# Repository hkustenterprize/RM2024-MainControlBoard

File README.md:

<div align='center'>
    <h1>灵活, 小巧, 可靠</h1>
</div>

<div align='center'>
    <h2>RM2024香港科技大学ENTERPRIZE</h2>
</div>

<div align='center'>
    <h1>G4主控板硬件开源</h1>
</div>

<div align='center'>

</div>

> 设计者：xzm/贤梓铭 zxianaa@connect.ust.hk
>
> 指导/提议：jyc/EthenJ, jason chan, ry/EEASEE, ofr, gzl/Fallengold, zzy
>
> 香港科技大学ENTERPRIZE战队 robomasterhkust@gmail.com

## 开源内容

~~~
RM2024_MainControlBoard
├── image
├── PDF Schematic               > PDF格式的原理图
├── RM2024_G473_MCB             > 核心板工程文件
├── RM2024_G473_MCB_Debugger    > 调试小板工程文件
├── RM2024_G473_MCB_EngExtend   > 单板方案工程扩展板工程文件 by ofr
├── RM2024_G473_MCB_StdExtend   > 常规扩展板工程文件
├── RM2024_G473_MCB_Shim.step   > 一体3D打印垫片step文件 by tsl
├── RM2024-Template-G473.ioc    > CubeMX模板
├── LICENSE
└── README.md
~~~

开源工程文件设计软件为 KiCAD, 建议使用 **KiCAD 8.0** 打开, 可以导入 **立创EDA**

每个工程文件文件夹中的内容:

~~~
xxx
├── bom             > 焊接小工具, 由 "Interactive HTML BOM" 插件生成
├── production      > 生产文件, 由 "Fabrication Toolkit" 插件生成
├── xxx.kicad_pcb   > PCB
├── xxx.kicad_pro   > 主工程, 通过双击这个启动KiCAD
└── xxx.kicad_sch   > 原理图
~~~

## 方案简介

整套主控板分为核心板(下板)和扩展板(上板), 两板之间使用80pin BTB接口连接; 核心板包含所有核心芯片, 而扩展板一般只用于引出接口 (以及buzzer, laser等功能), 需要特殊功能时则用作功能扩展

- MCU: STM32G473VET6
- IMU: ICM-42688P
- 磁力计: LIS3MDLTR
- TTL (硬件流控): CH343P *2 
- FDCAN *3
- RS485 (硬件流控) *1
- FLASH: W25N01GVZEIG

## 项目背景 & 应用情况

在 RoboMaster 2024 赛季, 由于队内自研的上一代主控板 (F407) 已经无法满足对机器人控制的需求, 于是产生了设计新型主控板的需求

在经过反复考虑和对比后, 我们选择了STM32G473VET6作为主控芯片, 主要原因如下

- 共有三路FDCAN外设, 可以控制更多电机
- 支持RS485硬件流控功能, 提升板间通讯的稳定性
- 相较于H7系列复杂度较低, 开发难度与F4系列近似

同时, 新一代主控板也有缩小体积的需求, 整个主控板大小控制在 **60×40×21mm**, 与大疆C板相近, 便于机械安装

<div align='center'>

</div>

最终, G4主控板被应用于ENTERPRIZE战队本赛季所有新研发的机器人, 并且为 **工程机器人的单板方案** (左图) 和 **双头哨兵** (右图) 打下基础; 同时也实现了较强的稳定性, 在几场比赛中从未出现因硬件不稳定而导致的问题

## 硬件连接框图(简化)

## 技术细节

### UART

虽然STM32G473的FDCAN等外设数量较多, 但UART的数量却只有5个, 如果用传统的方法对UART和相应功能进行一一绑定, 那么UART数量则不足以实现所有需要的功能

为了解决此问题, G4主控板在设计时利用了MCU外设内部的 **MUX**, 比如 UART1 可以配置为 PC4/PC5 或 PE0/PE1, 再与相应功能进行绑定, 以此来实现在不同应用场景中适应不同需求的能力

同时, 对于同一功能, G4主控板也提供了可以从多个外设的访问的选项; 比如对于接收机, 可以通过软件配置来使用 UART1 或 UART3 来接受数据

下面是具体的UART引脚配置, 以A/B/C后缀来表示同一UART的不同配置方式:

|        | TX   | RX   | DE   | CTS  | RTS  | 功能          |
| -----  | ---- | ---- | ---- | ---- | ---- | ----          |
| UART1A | PC4  | PC5  | -    | -    | -    | 裁判系统/图传  |
| UART1B | PE0  | PE1  | -    | -    | -    | 通用          |
| UART1C | -    | PA10 | -    | -    | -    | 接收机        |
| UART2A | PA2  | PA3  | -    | PA0  | PA1  | TTL1          |
| UART2B | PD5  | PD6  | -    | -    | -    | 通用          |  
| UART3A | PD8  | PD9  | -    | PD11 | PD12 | TTL2          |
| UART3B | PB10 | PE15 | -    | -    | -    | 通用          |  
| UART3C | -    | PB11 | -    | -    | -    | 接收机        | 
| UART4  | PC10 | PC11 | PA15 | -    | -    | RS485        |   
| UART5  | PC12 | PD2  | -    | -    | -    | 裁判系统/图传 |

下面是部分机器人上的UART功能分配:

|                   | UART1 | UART2 | UART3 | UART4 | UART5 |
| -----             | ----  | ----  | ----  | ----  | ----  |
| 步兵云台 | [C] 接收机 | [A] TTL1 | RESV | RS485 | [A] 图传 |
| 英雄云台 | [C] 接收机 | [A] TTL1 | RESV | RS485 | [A] 图传 |
| 哨兵云台 | [C] 接收机 | [A] TTL1 | [A] TTL2 | RS485 | [A] 图传 |
| 工程(单板) | [A] 裁判系统 | [B] 总线舵机  |  [C] 接收机 | RS485 | [A] 图传|
| 通用底盘  | RESV | RESV | RESV | RS485 | 裁判系统 |

### IMU

经过对比测试, IMU选择ICM-42688P, 并配合加热电阻实现恒温

经过测试, 选用1206封装, 36ohm的电阻可以满足恒温50°C的需求; 经测试, **恒温后纯IMU姿态解算5分钟内漂移小于1°**

同时, SPI信号线串接82ohm电阻, **通信速率可以稳定20M**

### RS485

|       | TX/D | RX/R | DE   |
| ----- | ---- | ---- | ---- |
| RS485 | PC10 | PC11 | PA15 |

主控板集成RS485来提供板间通信功能, 相较于串口, RS485可以使通信更加稳定(特别是过滑环时)

RS485 Transceiver选用SN75176AD, 可替换为其他芯片; 用SM712进行保护

使用STM32G473的RS485硬件流控功能后, **板间通信速率最高可以达到4.8M, 丢包率小于0.09%**

### CAN (×3)

|       | TX   | RX   |
| ----- | ---- | ---- |
| CAN1  | PD1  | PD0  |
| CAN2  | PB6  | PB5  |
| CAN3  | PB4  | PB3  |

CAN Transceiver选用SIT1042T/3, 可替换为其他芯片; 使用ESD1CAN进行保护

### USB-TTL (×2)

|       | TX   | RX   | CTS  | RTS  |
| ----- | ---- | ---- | ---- | ---- |
| TTL1 (UART2A)  | PA2  | PA3  | PA0  | PA1  |
| TTL2 (UART3A)  | PD8  | PD9  | PD11 | PD12 |

USB-TTL选用CH343P, 连接了RTS/CTS引脚来实现硬件流控, 使用TPD4E1U06DCKR进行保护

经测试**全双工条件下单向速率稳定2M, 实测丢包率0.006%左右**

连接了ACT指示灯, 方便观察连接状态, 此功能上场时非常有用(观察MiniPC是否断连)

### FLASH

|       | NCS   | CLK   | IO0  | IO1  | IO2  | IO3  |
| ----- | ---- | ---- | ---- | ---- | ---- | ---- |
| MCU   | PD3  | PF10  | PD4  | PC2  | PD3  | PC7  |

主控板集成FLASH用于记录数据, 便于调试分析; 型号选用W25N01GVZEIG; 通过QSPI与MCU进行通信

### 接收机

G4主控板采用MCU内部反相, 无需外部反相电路, 使用TPD4E1U06DCKR进行保护

可以通过 PB11(UART3) 或 PA10(UART1) 接收信号, 防止其中一个串口被占用的情况

### 硬件ID检测

通过短接扩展板上的三个ID焊盘, 可以配置主控板的 ID 和 Master/Slave角色

通过在代码中加入ID验证步骤, 可以防止因烧错代码导致 RS485 Transceiver 烧毁等问题

## 供电系统

### 电源框图

### 设计细节及原因

#### 3V3_MCU

由Buck电路而非LDO降压产生, 原因是STM32G473耗电量较大, 使用LDO会有潜在的过热问题; 

同时, 主控板上没有高精度ADC的需求, 故Buck电路的纹波对主控板正常工作影响不大

#### 3V3_IMU

专门用于IMU和磁力计的 VDD 供电网络, 防止其他噪声干扰IMU和磁力计; 

注意IMU和磁力计的 VDDIO 由 3V3_MCU 提供, 防止芯片内部通信部分对电源产生潜在干扰

#### 3V3_IO

主要用于于外部直接产生交互的外设的VIO;

与 3V3_MCU 隔离, 主要原因是为了防止外部收发信号时对核心供电的干扰, 比如 CAN 和 TTL 都直接使用 3V3_IO 作为生成信号电平的电源

#### 3V3_SWD

队内发生过因烧录器LDO损坏而导致 5V 烧毁MCU, 因此与 3V3_MCU 隔离, 通过二极管接入5V网络并同时防止倒灌;

此设计也产生了一个缺陷: 当主控板仅由烧录器供电是, 有时会因为压降太大而导致烧录不正常, 因此建议在有MiniPC USB供电或24V供电的情况下进行代码烧录和调试

#### 电压采样

主控板对 24V 和 5V 电源网络进行了电压采样;

前者是为了监测 24V 真实电源电压, 可以得到一些粗略电压信息;

后者是通过检测微小电压差异来确定目前的供电方式 (利用Buck输出 5.2V, USB供电 5.0V, SWD供电三种情况导致的差异), 并且在状态不正常时报警 (比如可以检测24V转5V的Buck损坏)

### 纹波测试
5V

3V3_MCU

## 复刻注意事项

- 目前包含的SMT生产文件格式适用于嘉立创, 如有需要请重新生成
- BTB很脆弱, 避免在不垫垫片的情况下安装
- 焊接IMU后不要用超声波洗板
- 如有任何问题, 欢迎联系 zxianaa@connect.ust.hk; wx: xianziming0531

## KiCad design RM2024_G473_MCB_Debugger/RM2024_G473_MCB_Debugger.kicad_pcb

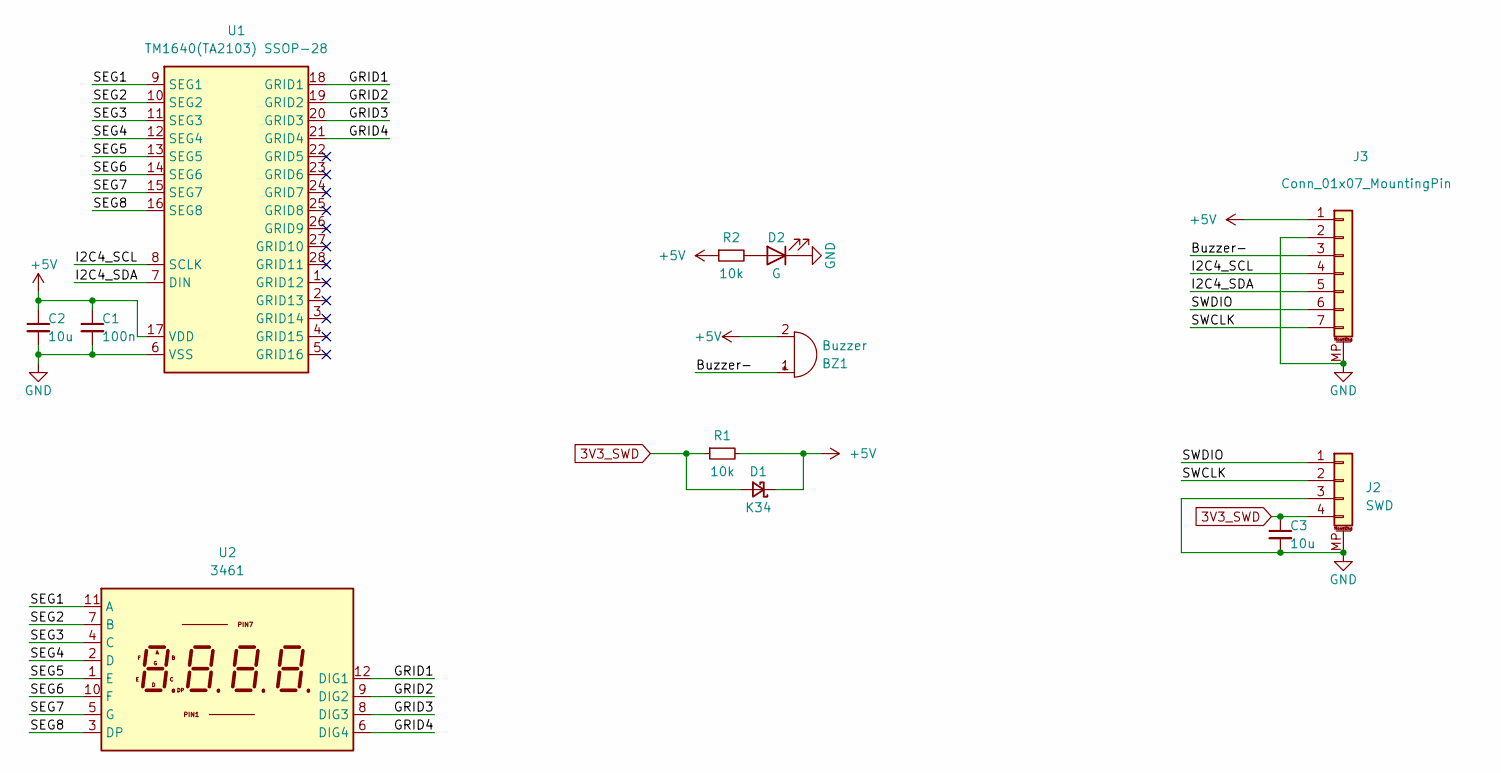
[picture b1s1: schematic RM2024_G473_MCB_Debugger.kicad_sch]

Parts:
BZ1: Buzzer; MLT-9032
C1: 100n; C_0603_1608Metric
C2, C3: 10u; C_0603_1608Metric
D1: K34; D_SMF
D2: G; LED_0603_1608Metric
J2: SWD; Molex_PicoBlade_53398-0471_1x04-1MP_P1.25mm_Vertical
J3: Conn_01x07_MountingPin; JST_GH_SM07B-GHS-TB_1x07-1MP_P1.25mm_Horizontal
R1, R2: 10k; R_0603_1608Metric
U1: TM1640(TA2103) SSOP-28; SSOP-28_3.9x9.9mm_P0.635mm
U2: 3461; LED-8888-3461

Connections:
3V3_SWD: C3.1, D1.2 (A), J2.4, R1.1
+5V: BZ1.2 (+), C1.1, C2.1, D1.1 (K), J3.1, R1.2, R2.1, U1.17 (VDD)
/Buzzer-: BZ1.1 (-), J3.3
/GRID1: U1.18 (GRID1), U2.12 (DIG1)
/GRID2: U1.19 (GRID2), U2.9 (DIG2)
/GRID3: U1.20 (GRID3), U2.8 (DIG3)
/GRID4: U1.21 (GRID4), U2.6 (DIG4)
/I2C4_SCL: J3.4, U1.8 (SCLK)
/I2C4_SDA: J3.5, U1.7 (DIN)
/SEG1: U1.9 (SEG1), U2.11 (A)
/SEG2: U1.10 (SEG2), U2.7 (B)
/SEG3: U1.11 (SEG3), U2.4 (C)
/SEG4: U1.12 (SEG4), U2.2 (D)
/SEG5: U1.13 (SEG5), U2.1 (E)
/SEG6: U1.14 (SEG6), U2.10 (F)
/SEG7: U1.15 (SEG7), U2.5 (G)
/SEG8: U1.16 (SEG8), U2.3 (DP)
/SWCLK: J2.2, J3.7
/SWDIO: J2.1, J3.6
GND: C1.2, C2.2, C3.2, D2.1 (K), J2.3, J2.MP (MountPin), J3.2, J3.MP (MountPin), U1.6 (VSS)
unnamed: D2.2 (A), R2.2

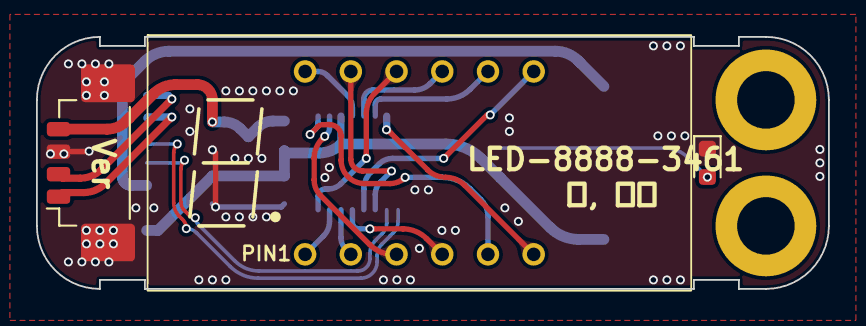
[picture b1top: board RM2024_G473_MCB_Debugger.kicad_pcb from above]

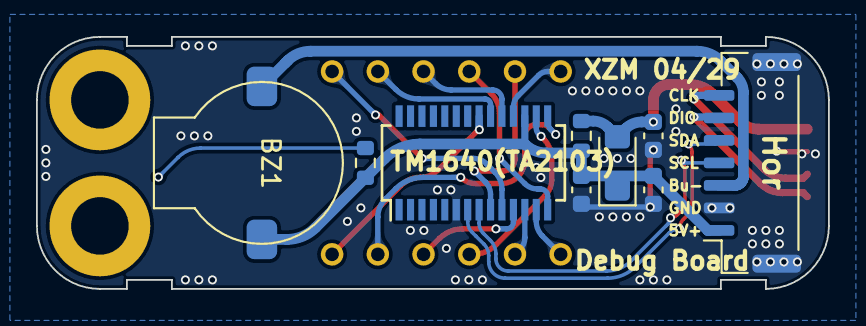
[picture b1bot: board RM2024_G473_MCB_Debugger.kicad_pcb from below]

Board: 2 copper layers, 44.0 x 14.0 mm, 12 parts (9 on the bottom side), 21 nets.

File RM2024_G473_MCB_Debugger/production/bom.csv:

Designator,Footprint,Quantity,Value,LCSC Part #
BZ1,MLT-9032,1,Buzzer,
C1,0603,1,100n,
"C2, C3",0603,2,10u,
D1,D_SMF,1,K34,
D2,0603,1,G,
J2,Molex_PicoBlade_53398-0471_1x04-1MP_P1.25mm_Vertical,1,SWD,
J3,JST_GH_SM07B-GHS-TB_1x07-1MP_P1.25mm_Horizontal,1,Conn_01x07_MountingPin,
"R1, R2",0603,2,10k,
U1,SSOP-28_3.9x9.9mm_P0.635mm,1,TM1640(TA2103) SSOP-28,
U2,LED-8888-3461,1,3461,

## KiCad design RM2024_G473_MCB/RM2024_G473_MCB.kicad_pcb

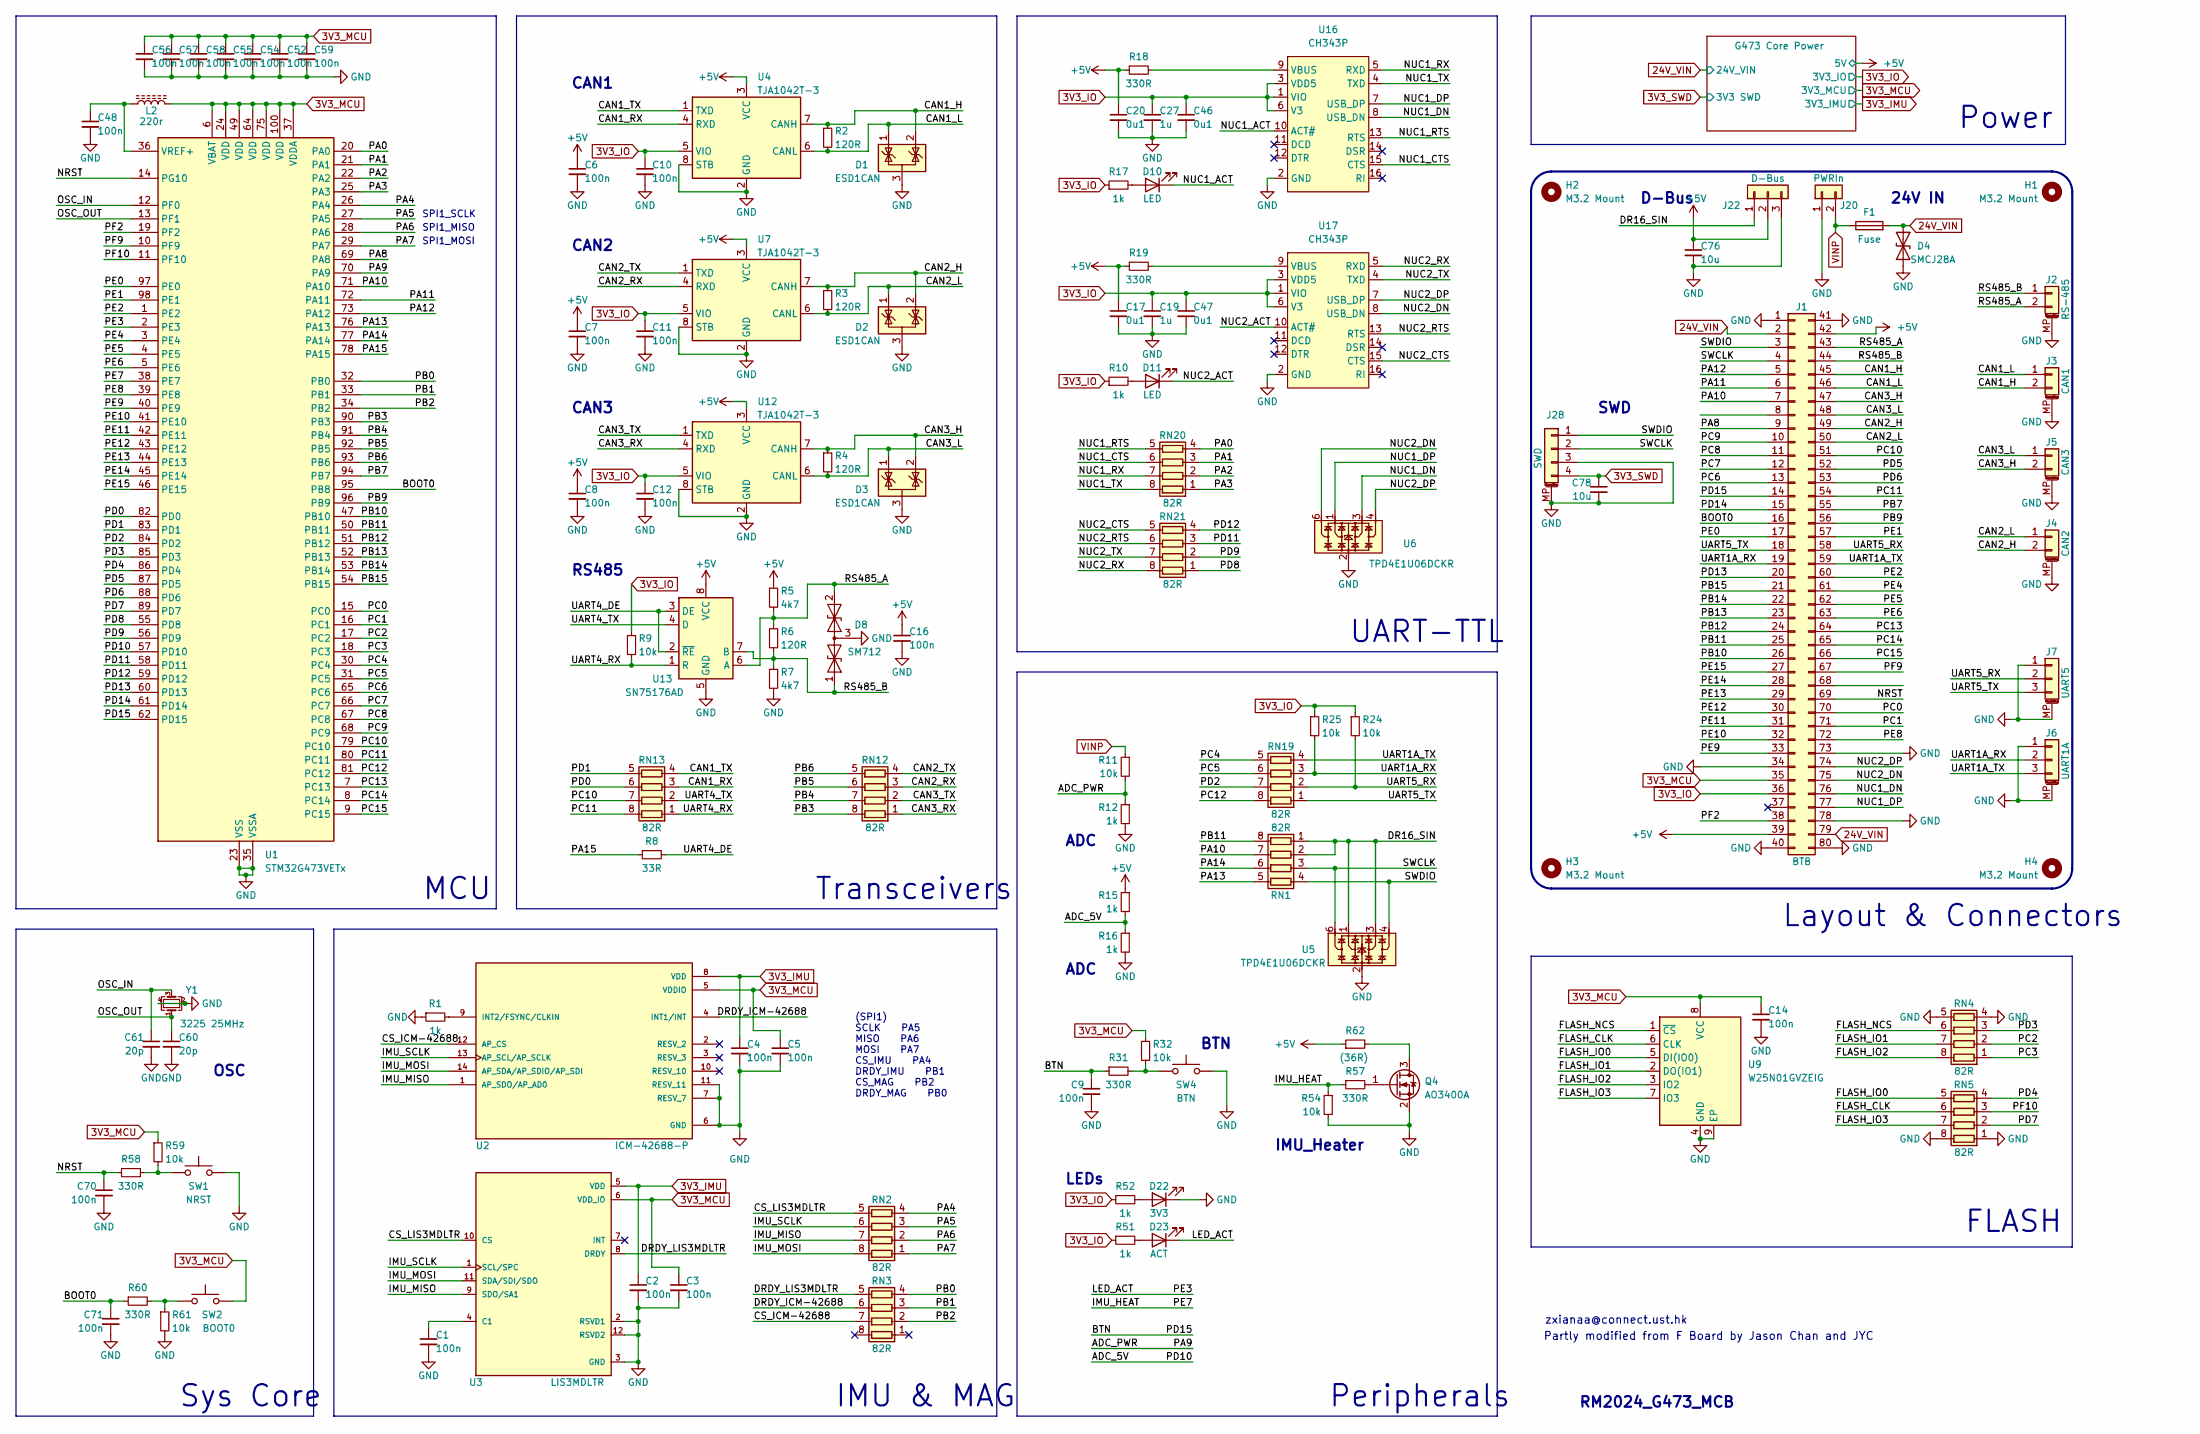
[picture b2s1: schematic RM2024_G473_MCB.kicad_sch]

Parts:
C1, C2, C3, C4, C5, C6, C7, C8, C9, C10, C11, C12, C14, C16, C48, C52, C54, C55, C56, C57, C58, C59, C70, C71: 100n; C_0603_1608Metric
C17, C20, C46, C47: 0u1; C_0603_1608Metric
C19, C27: 1u; C_0603_1608Metric
C60, C61: 20p; C_0603_1608Metric
C76, C78: 10u; C_0603_1608Metric
D1, D2, D3: ESD1CAN; SOT-23
D4: SMCJ28A; D_SMC
D8: SM712; SOT-23
D10, D11: LED; LED_0603_1608Metric
D22: 3V3; LED_0603_1608Metric
D23: ACT; LED_0603_1608Metric
F1: Fuse; Fuse_1206_3216Metric
H1, H2, H3, H4: M3.2 Mount; MountingHole_3.2mm_M3_DIN965_Pad
J1: BTB; BTB_P0.8mm_2x40pin_F
J2: RS-485; JST_GH_SM02B-GHS-TB_1x02-1MP_P1.25mm_Horizontal
J3: CAN1; JST_GH_SM02B-GHS-TB_1x02-1MP_P1.25mm_Horizontal
J4: CAN2; JST_GH_SM02B-GHS-TB_1x02-1MP_P1.25mm_Horizontal
J5: CAN3; JST_GH_SM02B-GHS-TB_1x02-1MP_P1.25mm_Horizontal
J6: UART1A; JST_GH_SM03B-GHS-TB_1x03-1MP_P1.25mm_Horizontal
J7: UART5; JST_GH_SM03B-GHS-TB_1x03-1MP_P1.25mm_Horizontal
J20: PWRIn; AMASS_XT30U-M_1x02_P5.0mm_Vertical
J22: D-Bus; PinHeader_1x03_P2.54mm_Vertical
J28: SWD; Molex_PicoBlade_53261-0471_1x04-1MP_P1.25mm_Horizontal
L2: 220r; L_0603_1608Metric
Q4: AO3400A; SOT-23
R1, R10, R12, R15, R16, R17, R51, R52: 1k; R_0603_1608Metric
R2, R3, R4, R6: 120R; R_0603_1608Metric
R5, R7: 4k7; R_0603_1608Metric
R8: 33R; R_0603_1608Metric
R9, R11, R24, R25, R32, R54, R59, R61: 10k; R_0603_1608Metric
R18, R19, R31, R57, R58, R60: 330R; R_0603_1608Metric
R62: (36R); R_1206_3216Metric
RN1, RN2, RN3, RN4, RN5, RN12, RN13, RN19, RN20, RN21: 82R; R_Array_Concave_4x0603
SW1: NRST; Panasonic_EVQPUL_EVQPUC
SW2: BOOT0; Panasonic_EVQPUL_EVQPUC
SW4: BTN; Panasonic_EVQPUL_EVQPUC
U1: STM32G473VETx; LQFP-100_14x14mm_P0.5mm
U2: ICM-42688-P; PQFN50P300X250X97-14N; PARTREV 1.2
U3: LIS3MDLTR; XDCR_LIS3MDLTR; PARTREV 6
U4, U7, U12: TJA1042T-3; SOIC-8_3.9x4.9mm_P1.27mm
U5, U6: TPD4E1U06DCKR; SOT-363_SC-70-6
U9: W25N01GVZEIG; WSON-8-1EP_8x6mm_P1.27mm_EP3.4x4.3mm
U13: SN75176AD; SOIC-8_3.9x4.9mm_P1.27mm
U16, U17: CH343P; TQFN-16-1EP_3x3mm_P0.5mm_EP1.6x1.6mm
Y1: 3225 25MHz; Crystal_SMD_3225-4Pin_3.2x2.5mm

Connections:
3V3_IMU: C2.1, C4.1, U2.8 (VDD), U3.5 (VDD); also elsewhere on the board
3V3_IO: C10.1, C11.1, C12.1, C19.1, C27.1, C46.1, C47.1, J1.36, R9.1, R10.1, R17.1, R24.1, R25.1, R51.1, R52.1, U4.5 (VIO), U7.5 (VIO), U12.5 (VIO), U16.1 (VIO), U16.3 (VDD5), U16.6 (V3), U17.1 (VIO), U17.3 (VDD5), U17.6 (V3); also elsewhere on the board
3V3_MCU: C3.1, C5.1, C14.1, C52.1, C54.1, C55.1, C56.1, C57.1, C58.1, C59.1, J1.35, L2.2, R32.1, R59.1, SW2.2, U1.6 (VBAT), U1.24 (VDD), U1.37 (VDDA), U1.49 (VDD), U1.64 (VDD), U1.75 (VDD), U1.100 (VDD), U2.5 (VDDIO), U3.6 (VDD_IO), U9.8 (VCC); also elsewhere on the board
3V3_SWD: C78.1, J28.4; also elsewhere on the board
24V_VIN: D4.1 (A1), F1.2, J1.2, J1.79; also elsewhere on the board
+5V: C6.1, C7.1, C8.1, C16.1, C17.1, C20.1, C76.1, J1.39, J1.42, J22.2, R5.1, R15.1, R18.1, R19.1, R62.1, U4.3 (VCC), U7.3 (VCC), U12.3 (VCC), U13.8 (VCC); also elsewhere on the board
/ADC_5V: R15.2, R16.1, U1.57 (PD10)
/ADC_PWR: R11.2, R12.1, U1.70 (PA9)
/BOOT0: C71.1, J1.16, R60.1, U1.95 (PB8)
/BTN: C9.1, J1.14, R31.1, U1.62 (PD15)
/CAN1_H: D1.2 (K), J1.45, J3.2, R2.1, U4.7 (CANH)
/CAN1_L: D1.1 (K), J1.46, J3.1, R2.2, U4.6 (CANL)
/CAN1_RX: RN13.3 (R3.1), U4.4 (RXD)
/CAN1_TX: RN13.4 (R4.1), U4.1 (TXD)
/CAN2_H: D2.2 (K), J1.49, J4.2, R3.1, U7.7 (CANH)
/CAN2_L: D2.1 (K), J1.50, J4.1, R3.2, U7.6 (CANL)
/CAN2_RX: RN12.3 (R3.1), U7.4 (RXD)
/CAN2_TX: RN12.4 (R4.1), U7.1 (TXD)
/CAN3_H: D3.2 (K), J1.47, J5.2, R4.1, U12.7 (CANH)
/CAN3_L: D3.1 (K), J1.48, J5.1, R4.2, U12.6 (CANL)
/CAN3_RX: RN12.1 (R1.1), U12.4 (RXD)
/CAN3_TX: RN12.2 (R2.1), U12.1 (TXD)
/CS_ICM-42688: RN3.7 (R2.2), U2.12 (AP_CS)
/CS_LIS3MDLTR: RN2.5 (R4.2), U3.10 (CS)
/DR16_SIN: J22.1, RN1.1 (R1.1), RN1.2 (R2.1), U5.1, U5.3
/DRDY_ICM-42688: RN3.6 (R3.2), U2.4 (INT1/INT)
/DRDY_LIS3MDLTR: RN3.5 (R4.2), U3.8 (DRDY)
/FLASH_CLK: RN5.6 (R3.2), U9.6 (CLK)
/FLASH_IO0: RN5.5 (R4.2), U9.5 (DI(IO0))
/FLASH_IO1: RN4.7 (R2.2), U9.2 (DO(IO1))
/FLASH_IO2: RN4.8 (R1.2), U9.3 (IO2)
/FLASH_IO3: RN5.7 (R2.2), U9.7 (IO3)
/FLASH_NCS: RN4.6 (R3.2), U9.1 (~CS)
/IMU_HEAT: R54.1, R57.1, U1.38 (PE7)
/IMU_MISO: RN2.7 (R2.2), U2.1 (AP_SDO/AP_AD0), U3.9 (SDO/SA1)
/IMU_MOSI: RN2.8 (R1.2), U2.14 (AP_SDA/AP_SDIO/AP_SDI), U3.11 (SDA/SDI/SDO)
/IMU_SCLK: RN2.6 (R3.2), U2.13 (AP_SCL/AP_SCLK), U3.1 (SCL/SPC)
/LED_ACT: D23.1 (K), U1.2 (PE3)
/NRST: C70.1, J1.69, R58.1, U1.14 (PG10)
/NUC1_ACT: D10.1 (K), U16.10 (ACT#)
/NUC1_CTS: RN20.6 (R3.2), U16.15 (CTS)
/NUC1_DN: J1.76, U6.3, U16.8 (USB_DN)
/NUC1_DP: J1.77, U6.1, U16.7 (USB_DP)
/NUC1_RTS: RN20.5 (R4.2), U16.13 (RTS)
/NUC1_RX: RN20.7 (R2.2), U16.5 (RXD)
/NUC1_TX: RN20.8 (R1.2), U16.4 (TXD)
/NUC2_ACT: D11.1 (K), U17.10 (ACT#)
/NUC2_CTS: RN21.5 (R4.2), U17.15 (CTS)
/NUC2_DN: J1.75, U6.6, U17.8 (USB_DN)
/NUC2_DP: J1.74, U6.4, U17.7 (USB_DP)
/NUC2_RTS: RN21.6 (R3.2), U17.13 (RTS)
/NUC2_RX: RN21.8 (R1.2), U17.5 (RXD)
/NUC2_TX: RN21.7 (R2.2), U17.4 (TXD)
/OSC_IN: C61.1, U1.12 (PF0), Y1.3
/OSC_OUT: C60.1, U1.13 (PF1), Y1.1
/PA0: RN20.4 (R4.1), U1.20 (PA0)
/PA1: RN20.3 (R3.1), U1.21 (PA1)
/PA2: RN20.2 (R2.1), U1.22 (PA2)
/PA3: RN20.1 (R1.1), U1.25 (PA3)
/PA4: RN2.4 (R4.1), U1.26 (PA4)
/PA5: RN2.3 (R3.1), U1.27 (PA5)
/PA6: RN2.2 (R2.1), U1.28 (PA6)
/PA7: RN2.1 (R1.1), U1.29 (PA7)
/PA8: J1.9, U1.69 (PA8)
/PA10: J1.7, RN1.7 (R2.2), U1.71 (PA10)
/PA11: J1.6, U1.72 (PA11)
/PA12: J1.5, U1.73 (PA12)
/PA13: RN1.5 (R4.2), U1.76 (PA13)
/PA14: RN1.6 (R3.2), U1.77 (PA14)
/PA15: R8.1, U1.78 (PA15)
/PB0: RN3.4 (R4.1), U1.32 (PB0)
/PB1: RN3.3 (R3.1), U1.33 (PB1)
/PB2: RN3.2 (R2.1), U1.34 (PB2)
/PB3: RN12.8 (R1.2), U1.90 (PB3)
/PB4: RN12.7 (R2.2), U1.91 (PB4)
/PB5: RN12.6 (R3.2), U1.92 (PB5)
/PB6: RN12.5 (R4.2), U1.93 (PB6)
/PB7: J1.55, U1.94 (PB7)
/PB9: J1.56, U1.96 (PB9)
/PB10: J1.26, U1.47 (PB10)
/PB11: J1.25, RN1.8 (R1.2), U1.50 (PB11)
/PB12: J1.24, U1.51 (PB12)
/PB13: J1.23, U1.52 (PB13)
/PB14: J1.22, U1.53 (PB14)
/PB15: J1.21, U1.54 (PB15)
/PC0: J1.70, U1.15 (PC0)
/PC1: J1.71, U1.16 (PC1)
/PC2: RN4.2 (R2.1), U1.17 (PC2)
/PC3: RN4.1 (R1.1), U1.18 (PC3)
/PC4: RN19.5 (R4.2), U1.30 (PC4)
/PC5: RN19.6 (R3.2), U1.31 (PC5)
/PC6: J1.13, U1.65 (PC6)
/PC7: J1.12, U1.66 (PC7)
/PC8: J1.11, U1.67 (PC8)
/PC9: J1.10, U1.68 (PC9)
/PC10: J1.51, RN13.7 (R2.2), U1.79 (PC10)
/PC11: J1.54, RN13.8 (R1.2), U1.80 (PC11)
/PC12: RN19.8 (R1.2), U1.81 (PC12)
/PC13: J1.64, U1.7 (PC13)
/PC14: J1.65, U1.8 (PC14)
/PC15: J1.66, U1.9 (PC15)
/PD0: RN13.6 (R3.2), U1.82 (PD0)
/PD1: RN13.5 (R4.2), U1.83 (PD1)
/PD2: RN19.7 (R2.2), U1.84 (PD2)
/PD3: RN4.3 (R3.1), U1.85 (PD3)
/PD4: RN5.4 (R4.1), U1.86 (PD4)
/PD5: J1.52, U1.87 (PD5)
/PD6: J1.53, U1.88 (PD6)
/PD7: RN5.2 (R2.1), U1.89 (PD7)
/PD8: RN21.1 (R1.1), U1.55 (PD8)
/PD9: RN21.2 (R2.1), U1.56 (PD9)
/PD11: RN21.3 (R3.1), U1.58 (PD11)
/PD12: RN21.4 (R4.1), U1.59 (PD12)
/PD13: J1.20, U1.60 (PD13)
/PD14: J1.15, U1.61 (PD14)
/PE0: J1.17, U1.97 (PE0)
/PE1: J1.57, U1.98 (PE1)
/PE2: J1.60, U1.1 (PE2)
/PE4: J1.61, U1.3 (PE4)
/PE5: J1.62, U1.4 (PE5)
/PE6: J1.63, U1.5 (PE6)
/PE8: J1.72, U1.39 (PE8)
/PE9: J1.33, U1.40 (PE9)
/PE10: J1.32, U1.41 (PE10)
/PE11: J1.31, U1.42 (PE11)
/PE12: J1.30, U1.43 (PE12)
/PE13: J1.29, U1.44 (PE13)
/PE14: J1.28, U1.45 (PE14)
/PE15: J1.27, U1.46 (PE15)
/PF2: J1.38, U1.19 (PF2)
/PF9: J1.67, U1.10 (PF9)
/PF10: RN5.3 (R3.1), U1.11 (PF10)
/RS485_A: D8.2 (A2), J1.43, J2.2, R5.2, R6.1, U13.6 (A)
/RS485_B: D8.1 (A1), J1.44, J2.1, R6.2, R7.1, U13.7 (B)
/SWCLK: J1.4, J28.2, RN1.3 (R3.1), U5.6
/SWDIO: J1.3, J28.1, RN1.4 (R4.1), U5.4
/UART1A_RX: J1.19, J6.2, R25.2, RN19.3 (R3.1)
/UART1A_TX: J1.59, J6.3, RN19.4 (R4.1)
/UART4_DE: R8.2, U13.2 (~RE), U13.3 (DE)
/UART4_RX: R9.2, RN13.1 (R1.1), U13.1 (R)
/UART4_TX: RN13.2 (R2.1), U13.4 (D)
/UART5_RX: J1.58, J7.2, R24.2, RN19.2 (R2.1)
/UART5_TX: J1.18, J7.3, RN19.1 (R1.1)
GND: C1.2, C2.2, C3.2, C4.2, C5.2, C6.2, C7.2, C8.2, C9.2, C10.2, C11.2, C12.2, C14.2, C16.2, C17.2, C19.2, C20.2, C27.2, C46.2, C47.2, C48.2, C52.2, C54.2, C55.2, C56.2, C57.2, C58.2, C59.2, C60.2, C61.2, C70.2, C71.2, C76.2, C78.2, D1.3 (A), D2.3 (A), D3.3 (A), D4.2 (A2), D8.3 (common), D22.1 (K), J1.1, J1.34, J1.40, J1.41, J1.73, J1.78, J1.80, J2.MP (MountPin), J3.MP (MountPin), J4.MP (MountPin), J5.MP (MountPin), J6.1, J6.MP (MountPin), J7.1, J7.MP (MountPin), J20.1, J22.3, J28.3, J28.MP (MountPin), Q4.2 (S), R1.1, R7.2, R12.2, R16.2, R54.2, R61.2, RN4.4 (R4.1), RN4.5 (R4.2), RN5.1 (R1.1), RN5.8 (R1.2), SW1.2, SW4.2, U1.23 (VSS), U1.35 (VSSA), U1.48 (VSS), U1.63 (VSS), U1.74 (VSS), U1.99 (VSS), U2.6 (GND), U2.7 (RESV_7), U2.11 (RESV_11), U3.2 (RSVD1), U3.3 (GND), U3.12 (RSVD2), U4.2 (GND), U4.8 (STB), U5.2, U6.2, U7.2 (GND), U7.8 (STB), U9.4 (GND), U9.9 (EP), U12.2 (GND), U12.8 (STB), U13.5 (GND), U16.2 (GND), U16.17 (GND), U17.2 (GND), U17.17 (GND), Y1.2, Y1.4; also elsewhere on the board
unnamed: D10.2 (A), R17.2
unnamed: D11.2 (A), R10.2
unnamed: D22.2 (A), R52.2
unnamed: D23.2 (A), R51.2
unnamed: Q4.3 (D), R62.2
unnamed: Q4.1 (G), R57.2
unnamed: R31.2, R32.2, SW4.1
unnamed: R58.2, R59.2, SW1.1
unnamed: R60.2, R61.1, SW2.1
unnamed: C48.1, L2.1, U1.36 (VREF+)
unnamed: R1.2, U2.9 (INT2/FSYNC/CLKIN)
unnamed: C1.1, U3.4 (C1)
unnamed: R18.2, U16.9 (VBUS)
unnamed: R19.2, U17.9 (VBUS)
VINP: F1.1, J20.2, R11.1

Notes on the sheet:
SPI1_MOSI
ADC
(SPI1) SCLK PA5 MISO PA6 MOSI PA7 CS_IMU PA4 DRDY_IMU PB1 CS_MAG PB2 DRDY_MAG PB0
BTN
FLASH
OSC
IMU & MAG
Power
CAN1
24V IN
IMU_Heater
Layout & Connectors
Transceivers
Partly modified from F Board by Jason Chan and JYC
CAN3
RS485
SWD
SPI1_SCLK
Peripherals
RM2024_G473_MCB
MCU
Sys Core
SPI1_MISO
UART-TTL
LEDs
D-Bus
zxianaa@connect.ust.hk
CAN2

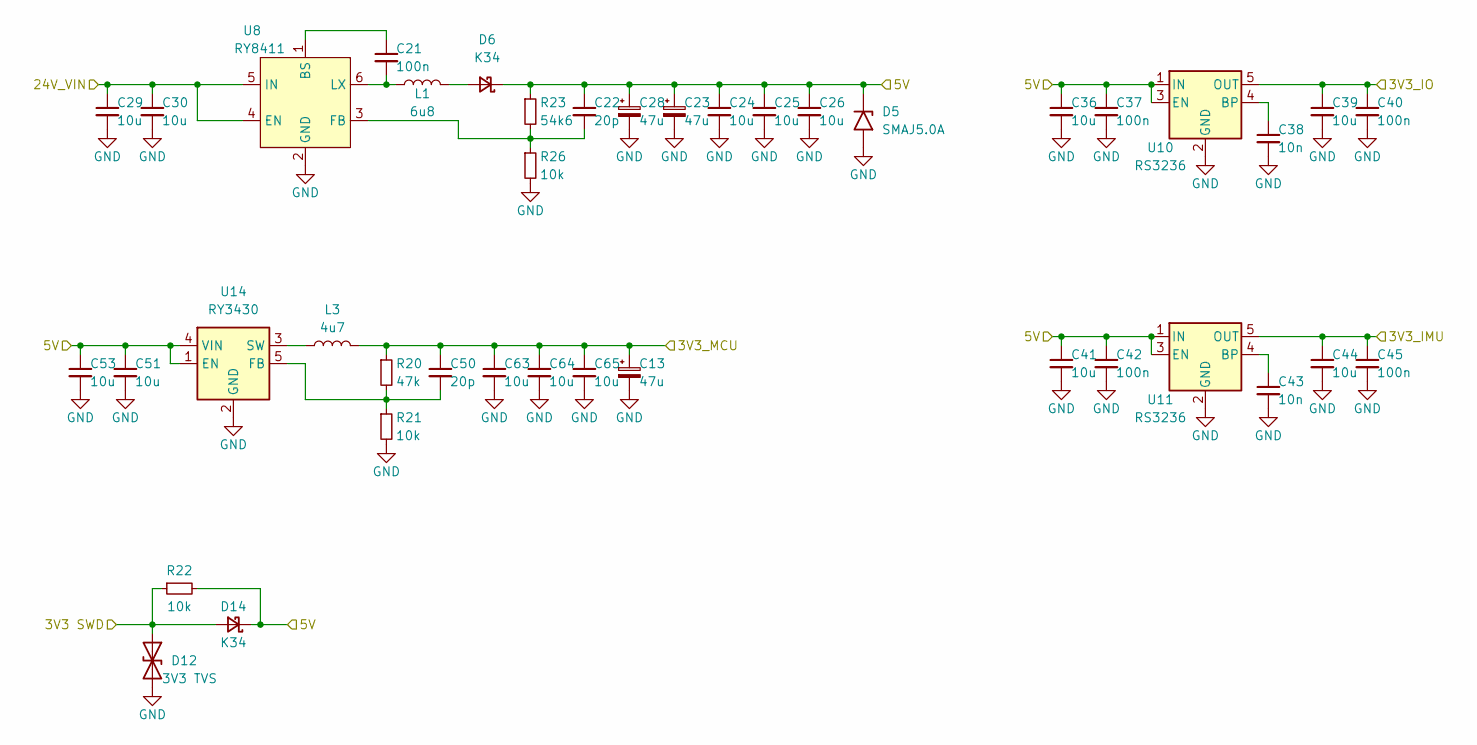
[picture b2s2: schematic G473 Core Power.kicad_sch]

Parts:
C13, C23, C28: 47u; CP_EIA-3216-18_Kemet-A_Pad1.58x1.35mm_HandSolder
C21, C37, C40, C42, C45: 100n; C_0603_1608Metric
C22, C50: 20p; C_0603_1608Metric
C24, C25, C26, C29, C30: 10u; C_1206_3216Metric
C36, C39, C41, C44, C51, C53, C63, C64, C65: 10u; C_0603_1608Metric
C38, C43: 10n; C_0603_1608Metric
D5: SMAJ5.0A; D_SMA
D6, D14: K34; D_SMF
D12: 3V3 TVS; D_SMF
L1: 6u8; L_Sunlord_MWSA0402S
L3: 4u7; L_Sunlord_MWSA0402S
R20: 47k; R_0603_1608Metric
R21, R22, R26: 10k; R_0603_1608Metric
R23: 54k6; R_0603_1608Metric
U8: RY8411; SOT-23-6
U10, U11: RS3236; SOT-23-5
U14: RY3430; SOT-23-5

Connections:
3V3_IMU: C44.1, C45.1, U11.5 (OUT); also elsewhere on the board
3V3_IO: C39.1, C40.1, U10.5 (OUT); also elsewhere on the board
3V3_MCU: C13.1, C50.1, C63.1, C64.1, C65.1, L3.2, R20.1; also elsewhere on the board
3V3_SWD: D12.1 (A1), D14.2 (A), R22.1; also elsewhere on the board
24V_VIN: C29.1, C30.1, U8.4 (EN), U8.5 (IN); also elsewhere on the board
+5V: C22.1, C23.1, C24.1, C25.1, C26.1, C28.1, C36.1, C37.1, C41.1, C42.1, C51.1, C53.1, D5.1 (A1), D6.1 (K), D14.1 (K), R22.2, R23.1, U10.1 (IN), U10.3 (EN), U11.1 (IN), U11.3 (EN), U14.1 (EN), U14.4 (VIN); also elsewhere on the board
GND: C13.2, C23.2, C24.2, C25.2, C26.2, C28.2, C29.2, C30.2, C36.2, C37.2, C38.2, C39.2, C40.2, C41.2, C42.2, C43.2, C44.2, C45.2, C51.2, C53.2, C63.2, C64.2, C65.2, D5.2 (A2), D12.2 (A2), R21.2, R26.2, U8.2 (GND), U10.2 (GND), U11.2 (GND), U14.2 (GND); also elsewhere on the board
unnamed: D6.2 (A), L1.2
unnamed: C21.1, U8.1 (BS)
unnamed: C22.2, R23.2, R26.1, U8.3 (FB)
unnamed: C21.2, L1.1, U8.6 (LX)
unnamed: C38.1, U10.4 (BP)
unnamed: C43.1, U11.4 (BP)
unnamed: C50.2, R20.2, R21.1, U14.5 (FB)
unnamed: L3.1, U14.3 (SW)

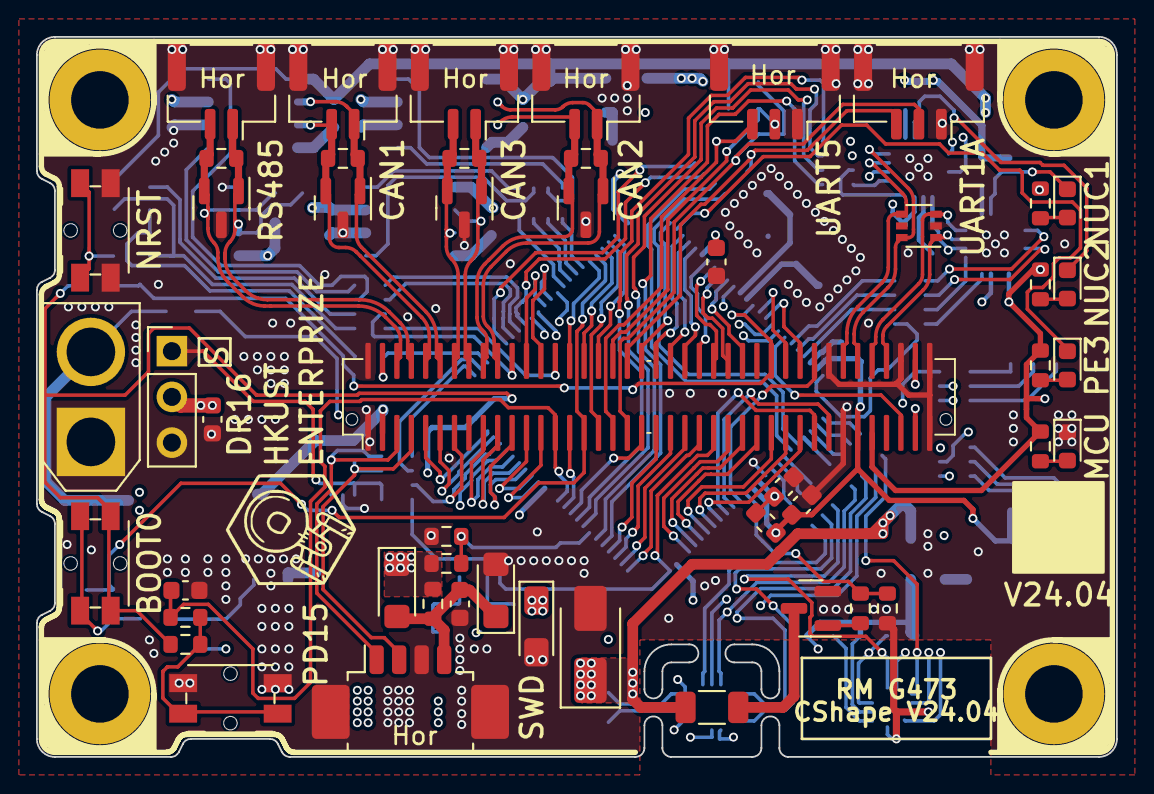
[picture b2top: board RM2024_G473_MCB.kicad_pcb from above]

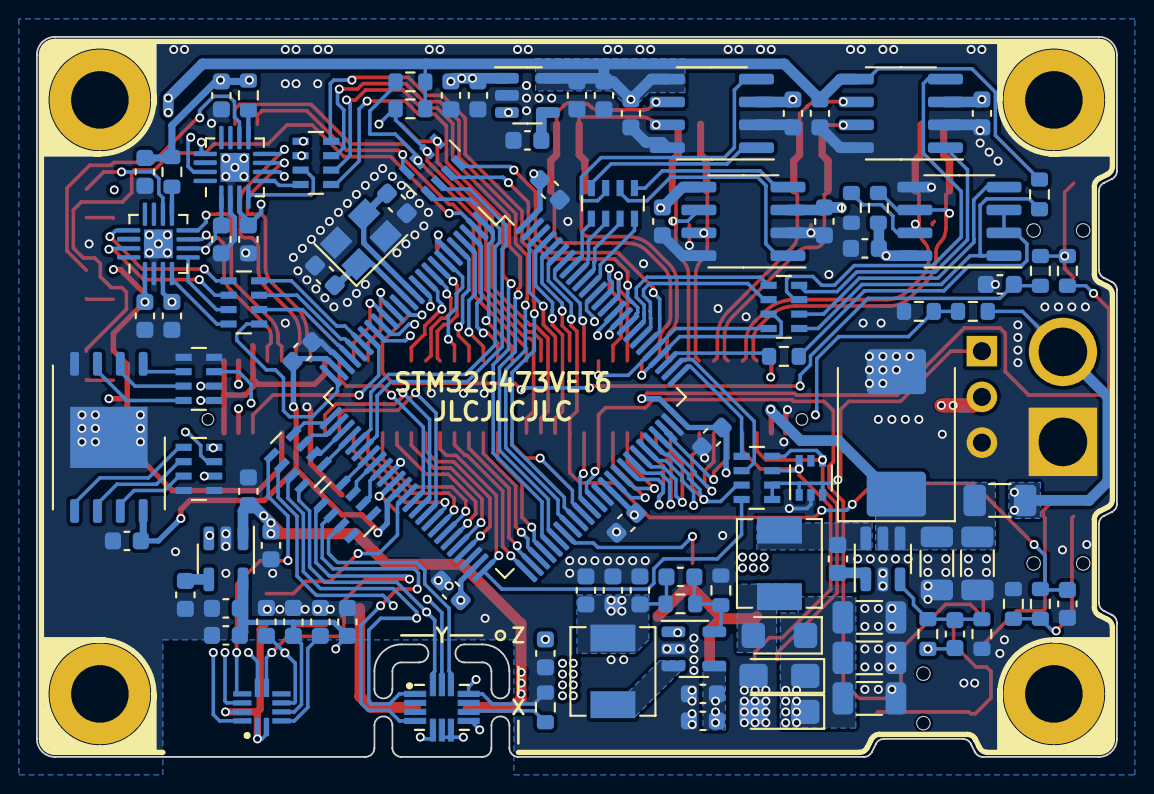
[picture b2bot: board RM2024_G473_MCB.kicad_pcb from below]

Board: 4 copper layers, 60.0 x 40.0 mm, 157 parts (103 on the bottom side), 167 nets.

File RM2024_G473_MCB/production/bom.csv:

Designator,Footprint,Quantity,Value,LCSC Part #
"C1, C10, C11, C12, C14, C16, C2, C21, C3, C37, C4, C40, C42, C45, C48, C5, C52, C54, C55, C56, C57, C58, C59, C6, C7, C70, C71, C8, C9",0603,29,100n,
"C13, C23, C28",CP_EIA-3216-18_Kemet-A_Pad1.58x1.35mm_HandSolder,3,47u,
"C17, C20, C46, C47",0603,4,0u1,
"C19, C27",0603,2,1u,
"C22, C50, C60, C61",0603,4,20p,
"C24, C25, C26, C29, C30",1206,5,10u,
"C36, C39, C41, C44, C51, C53, C63, C64, C65, C76, C78",0603,11,10u,
"C38, C43",0603,2,10n,
"D1, D2, D3",SOT-23,3,NUP2105L,
"D10, D11",0603,2,LED,
D12,D_SMF,1,3V3 TVS,
"D14, D6",D_SMF,2,K34,
D22,0603,1,3V3,
D23,0603,1,ACT,
D4,D_SMC,1,SMCJ28A,
D5,D_SMA,1,SMAJ5.0A,
D8,SOT-23,1,SM712,
F1,1206,1,Fuse,
"H1, H2, H3, H4",MountingHole_3.2mm_M3_DIN965_Pad,4,M3.2 Mount,
J1,BTB_P0.8mm_2x40pin_F,1,BTB,
J2,JST_GH_SM02B-GHS-TB_1x02-1MP_P1.25mm_Horizontal,1,RS-485,
J20,AMASS_XT30U-M_1x02_P5.0mm_Vertical,1,PWRIn,
J22,PinHeader_1x03_P2.54mm_Vertical,1,D-Bus,
J28,Molex_PicoBlade_53261-0471_1x04-1MP_P1.25mm_Horizontal,1,SWD,
J3,JST_GH_SM02B-GHS-TB_1x02-1MP_P1.25mm_Horizontal,1,CAN1,
J4,JST_GH_SM02B-GHS-TB_1x02-1MP_P1.25mm_Horizontal,1,CAN2,
J5,JST_GH_SM02B-GHS-TB_1x02-1MP_P1.25mm_Horizontal,1,CAN3,
J6,JST_GH_SM03B-GHS-TB_1x03-1MP_P1.25mm_Horizontal,1,UART1A,
J7,JST_GH_SM03B-GHS-TB_1x03-1MP_P1.25mm_Horizontal,1,UART5,
L1,L_Sunlord_MWSA0402S,1,6u8,
L2,0603,1,220r,
L3,L_Sunlord_MWSA0402S,1,4u7,
Q4,SOT-23,1,AO3400A,
"R1, R10, R12, R15, R16, R17, R51, R52",0603,8,1k,
"R11, R21, R22, R24, R25, R26, R32, R54, R59, R61, R9",0603,11,10k,
"R18, R19, R31, R57, R58, R60",0603,6,330R,
"R2, R3, R4, R6",0603,4,120R,
R20,0603,1,47k,
R23,0603,1,54k6,
"R5, R7",0603,2,4k7,
R62,1206,1,(36R),
R8,0603,1,33R,
"RN1, RN12, RN13, RN19, RN2, RN20, RN21, RN3, RN4, RN5",R_Array_Concave_4x0603,10,82R,
SW1,Panasonic_EVQPUL_EVQPUC,1,NRST,
SW2,Panasonic_EVQPUL_EVQPUC,1,BOOT0,
SW4,Panasonic_EVQPUL_EVQPUC,1,BTN,
U1,LQFP-100_14x14mm_P0.5mm,1,STM32G473VETx,
"U10, U11",SOT-23-5,2,RS3236,
"U12, U4, U7",SOIC-8_3.9x4.9mm_P1.27mm,3,TJA1042T-3,
U13,SOIC-8_3.9x4.9mm_P1.27mm,1,SN75176AD,
U14,SOT-23-5,1,RY3430,
"U16, U17",TQFN-16-1EP_3x3mm_P0.5mm_EP1.6x1.6mm,2,CH343P,
U2,PQFN50P300X250X97-14N,1,ICM-42688-P,
U3,XDCR_LIS3MDLTR,1,LIS3MDLTR,
"U5, U6",SOT-363_SC-70-6,2,TPD4E1U06DCKR,
U8,SOT-23-6,1,RY8411,
U9,WSON-8-1EP_8x6mm_P1.27mm_EP3.4x4.3mm,1,W25Q32JVZP,
Y1,Crystal_SMD_3225-4Pin_3.2x2.5mm,1,3225 25MHz,
